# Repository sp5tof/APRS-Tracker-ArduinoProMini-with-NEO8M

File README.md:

# APRS Tracker/Decoder for Baofeng based on ArduinoProMini, ESP32 & NEO8M GPS receiver module
This project is based on:

- Billy's project : https://github.com/billygr/arduino-aprs-tracker  - more informations: https://www.billy.gr/arduino-aprs-tracker/ &
- ESP32 iGate project https://github.com/nakhonthai/ESP32APRS_Audio

It consists of two independent uC: Arduino Pro-Mini for TNC transmition and ESP-Wroom32 with OLED board for visual decoding incoming APRS frames.
This is becouse I wasn't able to force Atmega328p with Arduino bootloader to decode any AX.25 frames using the another decoder idea :
https://github.com/chokelive/aprs_tnc .
From the other hand, ESP32 iGate standalone project doesn't seem to support the NEO8M GPS receiver. 
That's why I decided to use hybrid solution consists of two independent microprocessors.

Attached Eagle STL/BRD PCB allows to put them all together.

Baofeng is used as transceiver for this project and connected with two embedded mini-jacks sockets for TX/RX datas & PTT triggering.

I changed few things related to genuine project(Arduino Pro-Mini part):
- support for NEO8M GPS module (TinyGPS library has to be changed, I added the modified library here)
- small change made on original Billy's arduino code related to GPS module
- I used Arduino Pro mini in 5V version and adopted author's code to use this one
- added additional button for changing the APRS symbol(pressing it during the powering ON the device would change the symbol from "car" to "walking man")

I added external speaker with embedded preamp to the circuit as you can see on the schema. Baofeng turns off it's internal speaker when the mini-jack is plugged in. The idea behind the external speaker is about possibility of listening incoming APRS frames. Unfortunatelly, two audio receivers on the DAC output of esp32 makes overriding the audio line. That's why I had to add the audio splitter based on TL072.
  
Cable required for connecting the Baofeng with the device you have to make on your own. I wasn't able to find fully compatible 4-pins (MIC, SPK, PTT, GND) cable with any well-known online stores. However, you can try to order the baofeng audio cable from chinese online store, but the additional changes will have to be made according the the attached schema and pinout available in the net, f. ex : https://www.miklor.com/COM/images/dualplug.jpg .

For Arduino part, please compile and upload attached .ino code to the Arduino Pro-Mini.
Make necessary changes within the code according to your preferences (callsing, comment etc.).

In case of ESP32 part, please follow the manual within the link mentioned above on the nakhonthai github page. 
You have to flash the ESP board. You don't need to configure anything within the ESP32. 
Decoding functionality which is used in this project, works by default without any additional configurations steps to be performed.
I used the ESP-WROOM32 board with embedded OLED display, which works correctly(with version 13a of firmware version, added to this library. However, please use the newest available release on the nakhonthai github page, which should works correctly).

 Kuba/SP5TOF

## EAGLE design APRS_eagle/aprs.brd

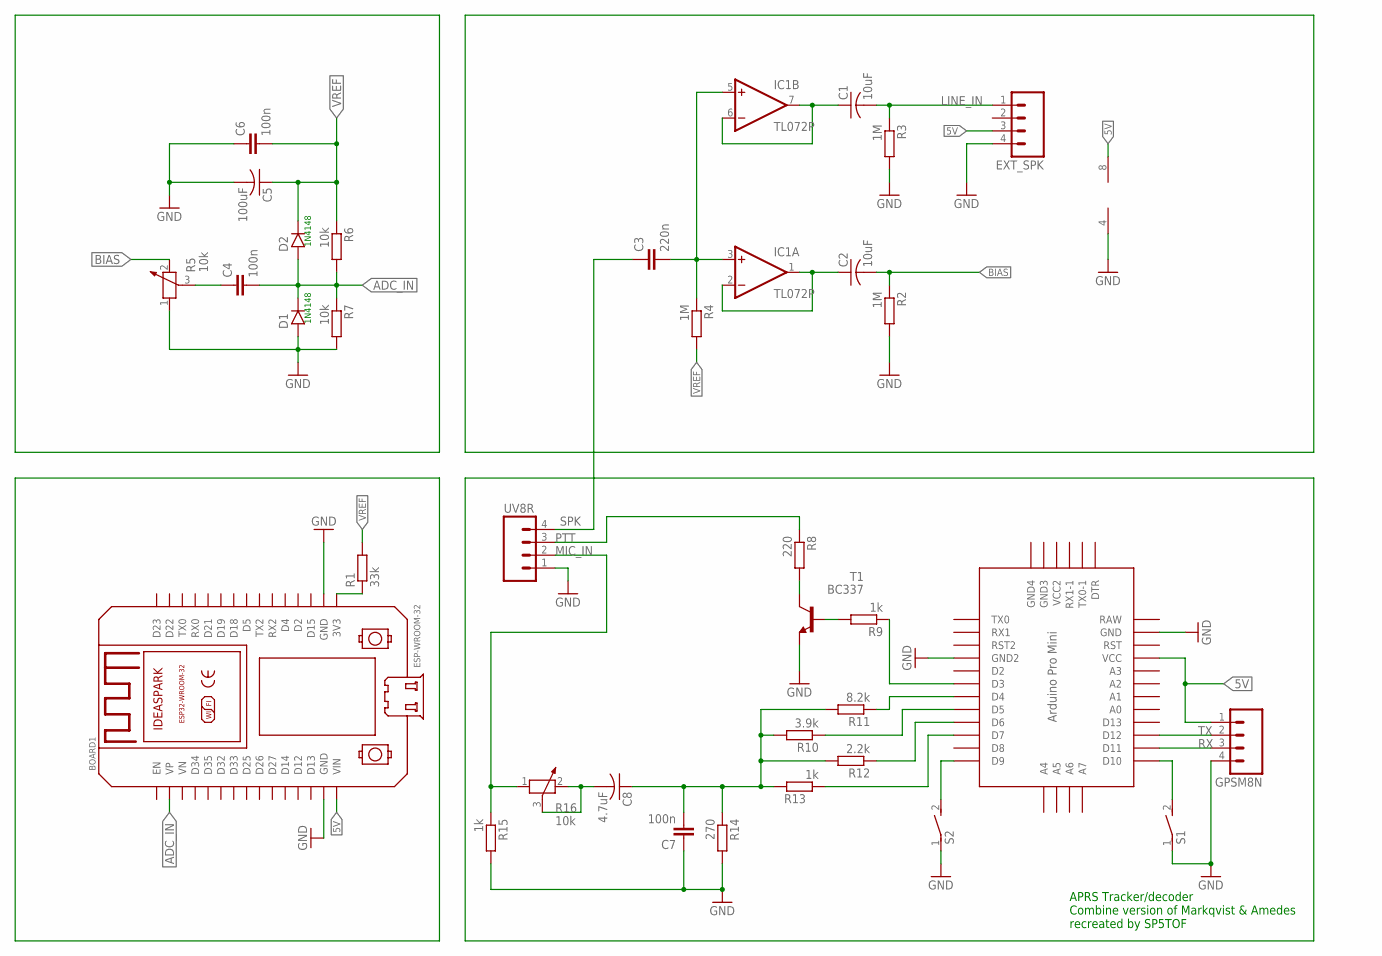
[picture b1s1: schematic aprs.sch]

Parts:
BOARD1: ESP32DEVKITV1; ESP32-DEVKITV1
C1, C2: 10uF; C050-035X075
C3: 220n; C025-025X050
C4, C6, C7: 100n; C025-025X050
C5: 100uF; C050-035X075
C8: 4.7uF; C050-035X075
D1, D2: 1N4148-3; DO35-3
EXT_SPK: M04; 04P
GPSM8N: M04; 04P
IC1: TL072P; DIL08
R1: 33k; 0207/7
R2, R3, R4: 1M; 0207/7
R5, R16: 10k; PT-10S
R6, R7: 10k; 0207/7
R8: 220; 0207/7
R9, R13, R15: 1k; 0207/7
R10: 3.9k; 0207/7
R11: 8.2k; 0207/7
R12: 2.2k; 0207/7
R14: 270; 0207/7
S1, S2: DS01E; DS-01
T1: BC337; TO92
U$1: PRO-MINI
UV8R: M04; 04P

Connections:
5V: BOARD1.VIN, EXT_SPK.3, GPSM8N.1, IC1.8 (V+), U$1.VCC
ADC_IN: BOARD1.VP, C4.2, D1.C, D2.A, R6.2, R7.1
BIAS: C2.2, R2.1, R5.2
GND: BOARD1.GND, BOARD1.GND@1 (GND), C5.2, C6.1, C7.1, D1.A, EXT_SPK.4, GPSM8N.4, IC1.4 (V-), R2.2, R3.2, R5.1, R7.2, R14.2, R15.2, S1.1, S2.1, T1.1 (E), U$1.GND, U$1.GND1 (GND2), UV8R.1
LINE_IN: C1.2, EXT_SPK.1, R3.1
MIC_IN: R15.1, R16.1, UV8R.2
unnamed: BOARD1.3V3, R1.1
unnamed: C1.1, IC1.6 (-IN), IC1.7 (OUT)
unnamed: C2.1, IC1.1 (OUT), IC1.2 (-IN)
unnamed: S2.2, U$1.D9
unnamed: C3.2, IC1.3 (+IN), IC1.5 (+IN), R4.1
unnamed: C4.1, R5.3
unnamed: S1.2, U$1.D10
unnamed: R9.1, U$1.D3
unnamed: R9.2, T1.2 (B)
unnamed: R8.2, T1.3 (C)
unnamed: R11.1, U$1.D4
unnamed: R10.1, U$1.D5
unnamed: R12.1, U$1.D6
unnamed: R13.1, U$1.D7
unnamed: C7.2, C8.1, R10.2, R11.2, R12.2, R13.2, R14.1
unnamed: C8.2, R16.2, R16.3
PTT: R8.1, UV8R.3
RAW: U$1.RAW
RX: GPSM8N.3, U$1.D11
SPK: C3.1, UV8R.4
TX: GPSM8N.2, U$1.D12
VREF: C5.1, C6.2, D2.C, R1.2, R4.2, R6.1

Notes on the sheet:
1N4148
APRS Tracker/decoder Combine version of Markqvist & Amedes recreated by SP5TOF

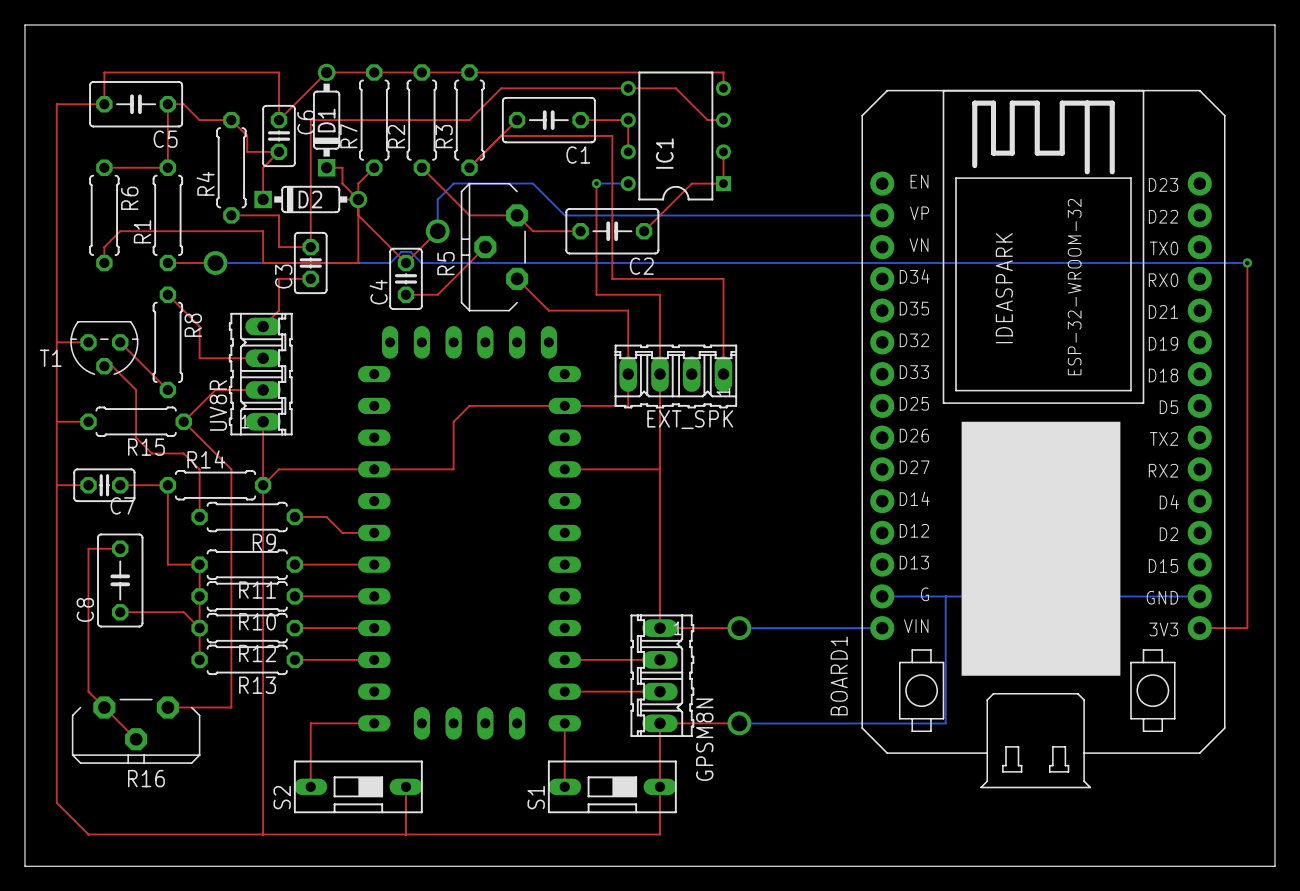
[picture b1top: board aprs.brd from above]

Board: 2 copper layers, 100.0 x 67.3 mm, 35 parts (0 on the bottom side), 27 nets.
